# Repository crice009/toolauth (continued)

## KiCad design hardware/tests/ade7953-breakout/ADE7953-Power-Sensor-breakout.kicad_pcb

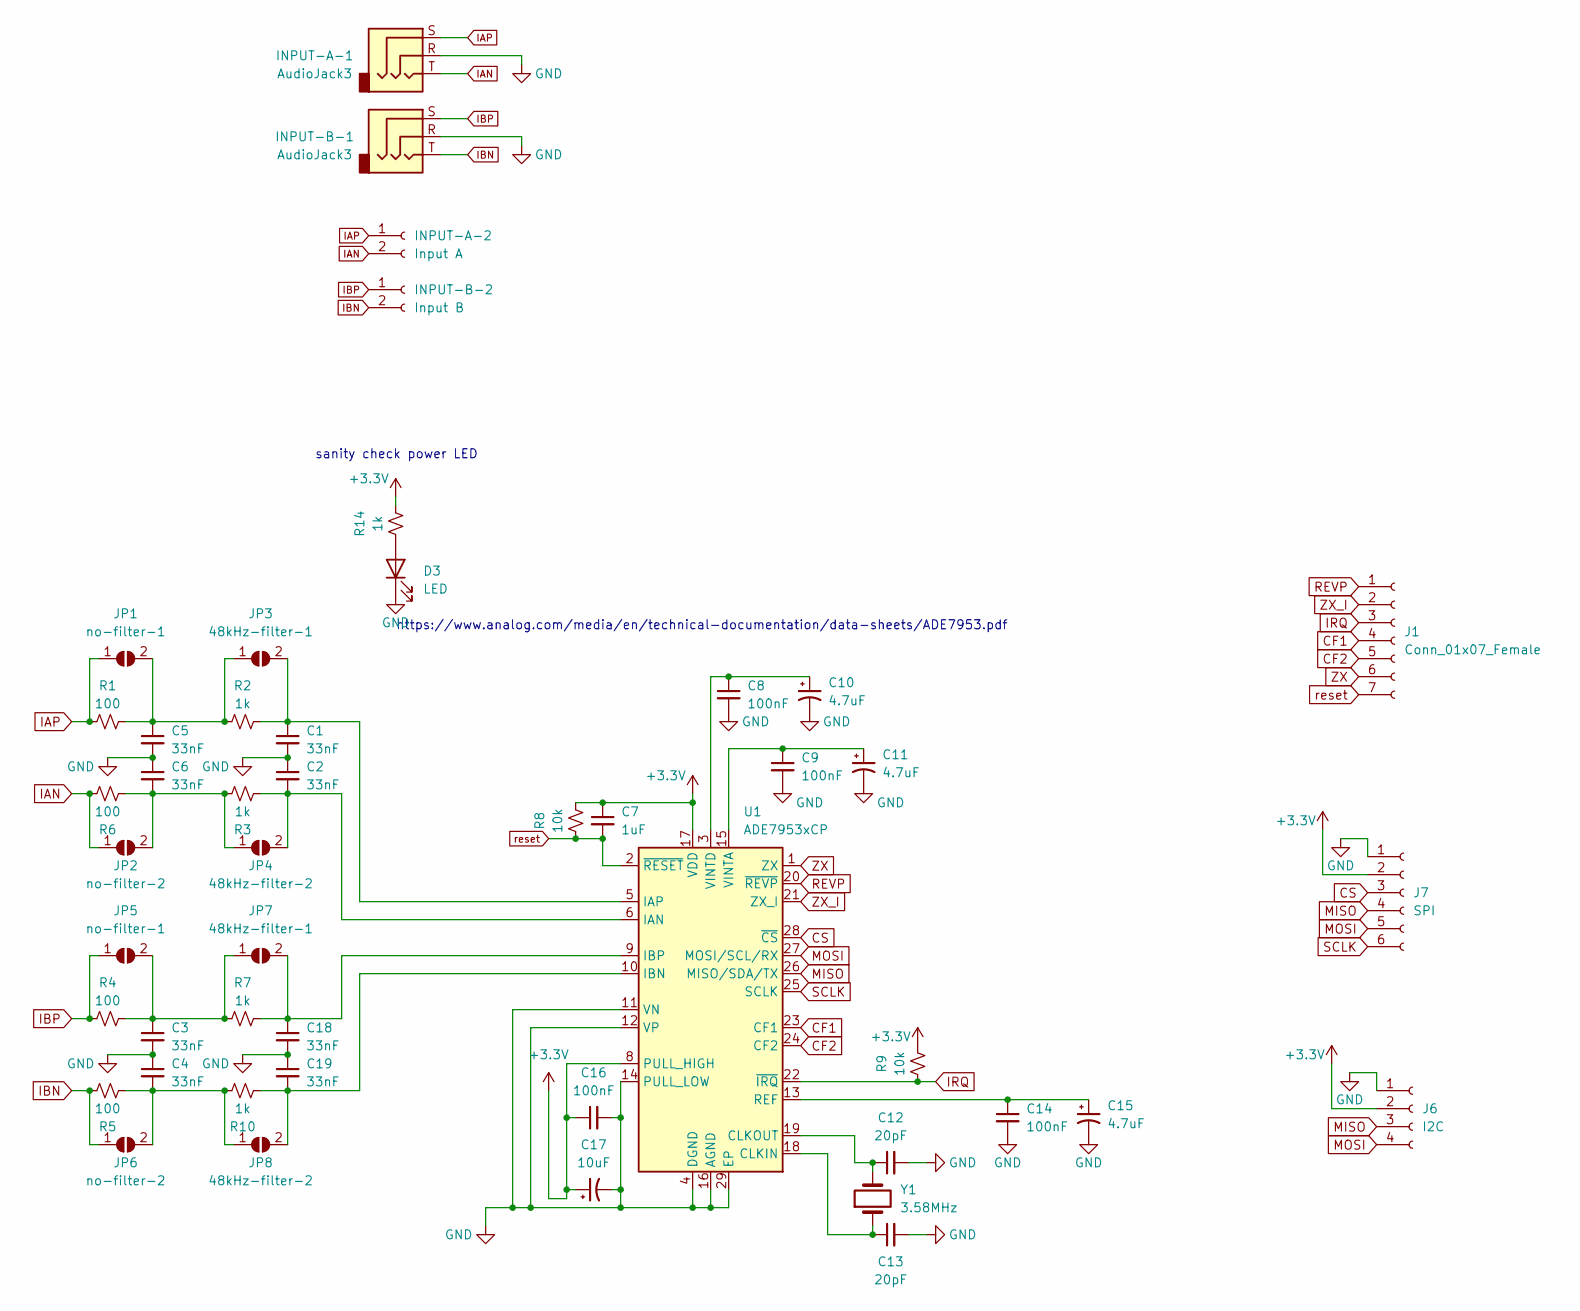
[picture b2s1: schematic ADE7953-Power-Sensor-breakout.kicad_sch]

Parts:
C1, C2, C3, C4, C5, C6, C18, C19: 33nF; C_0201_0603Metric
C7: 1uF; C_0201_0603Metric
C8, C9, C14, C16: 100nF; C_0201_0603Metric
C10, C11, C15: 4.7uF; CP_Radial_D5.0mm_P2.00mm
C12, C13: 20pF; C_0201_0603Metric
C17: 10uF; CP_Radial_D5.0mm_P2.00mm
D3: LED; LED_0201_0603Metric_Pad0.64x0.40mm_HandSolder
INPUT-A-1: AudioJack3; Jack_3.5mm_CUI_SJ1-3523N_Horizontal
INPUT-A-2: Input A; PinHeader_1x02_P2.54mm_Vertical
INPUT-B-1: AudioJack3; Jack_3.5mm_CUI_SJ1-3523N_Horizontal
INPUT-B-2: Input B; PinHeader_1x02_P2.54mm_Vertical
J1: Conn_01x07_Female; PinHeader_1x07_P2.54mm_Vertical
J6: I2C; PinHeader_1x04_P2.54mm_Vertical
J7: SPI; PinHeader_1x06_P2.54mm_Vertical
JP1, JP5: no-filter-1; SolderJumper-2_P1.3mm_Open_RoundedPad1.0x1.5mm
JP2, JP6: no-filter-2; SolderJumper-2_P1.3mm_Open_RoundedPad1.0x1.5mm
JP3, JP7: 48kHz-filter-1; SolderJumper-2_P1.3mm_Open_RoundedPad1.0x1.5mm
JP4, JP8: 48kHz-filter-2; SolderJumper-2_P1.3mm_Open_RoundedPad1.0x1.5mm
R1, R4, R5, R6: 100; R_0201_0603Metric
R2, R3, R7, R10, R14: 1k; R_0201_0603Metric
R8, R9: 10k; R_0201_0603Metric
U1: ADE7953xCP; LFCSP-28-1EP_5x5mm_P0.5mm_EP3.14x3.14mm
Y1: 3.58MHz; Crystal_HC49-4H_Vertical

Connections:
+3V3: C7.1, C16.1, C17.1, J6.2, J7.2, R8.2, R9.2, R14.2, U1.7 (PULL_HIGH), U1.8 (PULL_HIGH), U1.17 (VDD)
CF1: J1.4, U1.23 (CF1)
CF2: J1.5, U1.24 (CF2)
CS: J7.3, U1.28 (~CS)
GND: C1.2, C2.1, C3.2, C4.1, C5.2, C6.1, C8.2, C9.2, C10.2, C11.2, C12.2, C13.2, C14.2, C15.2, C16.2, C17.2, C18.2, C19.1, D3.1 (K), INPUT-A-1.R, INPUT-B-1.R, J6.1, J7.1, U1.4 (DGND), U1.11 (VN), U1.12 (VP), U1.14 (PULL_LOW), U1.16 (AGND), U1.29 (EP)
IAN: INPUT-A-1.T, INPUT-A-2.2, JP2.1 (A), R6.2
IAP: INPUT-A-1.S, INPUT-A-2.1, JP1.1 (A), R1.1
IBN: INPUT-B-1.T, INPUT-B-2.2, JP6.1 (A), R5.2
IBP: INPUT-B-1.S, INPUT-B-2.1, JP5.1 (A), R4.1
IRQ: J1.3, R9.1, U1.22 (~IRQ)
MISO: J6.3, J7.4, U1.26 (MISO/SDA/TX)
MOSI: J6.4, J7.5, U1.27 (MOSI/SCL/RX)
unnamed: C3.1, JP5.2 (B), JP7.1 (A), R4.2, R7.1
unnamed: C4.2, JP6.2 (B), JP8.1 (A), R5.1, R10.2
unnamed: C8.1, C10.1, U1.3 (VINTD)
unnamed: C9.1, C11.1, U1.15 (VINTA)
unnamed: C12.1, U1.19 (CLKOUT), Y1.2
unnamed: C13.1, U1.18 (CLKIN), Y1.1
unnamed: C14.1, C15.1, U1.13 (REF)
unnamed: D3.2 (A), R14.1
unnamed: C5.1, JP1.2 (B), JP3.1 (A), R1.2, R2.1
unnamed: C6.2, JP2.2 (B), JP4.1 (A), R3.2, R6.1
unnamed: C1.1, JP3.2 (B), R2.2, U1.5 (IAP)
unnamed: C2.2, JP4.2 (B), R3.1, U1.6 (IAN)
unnamed: C18.1, JP7.2 (B), R7.2, U1.9 (IBP)
unnamed: C19.2, JP8.2 (B), R10.1, U1.10 (IBN)
REVP: J1.1, U1.20 (~REVP)
SCLK: J7.6, U1.25 (SCLK)
ZX: J1.6, U1.1 (ZX)
ZX_I: J1.2, U1.21 (ZX_I)
reset: C7.2, J1.7, R8.1, U1.2 (~RESET)

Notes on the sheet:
sanity check power LED
https://www.analog.com/media/en/technical-documentation/data-sheets/ADE7953.pdf

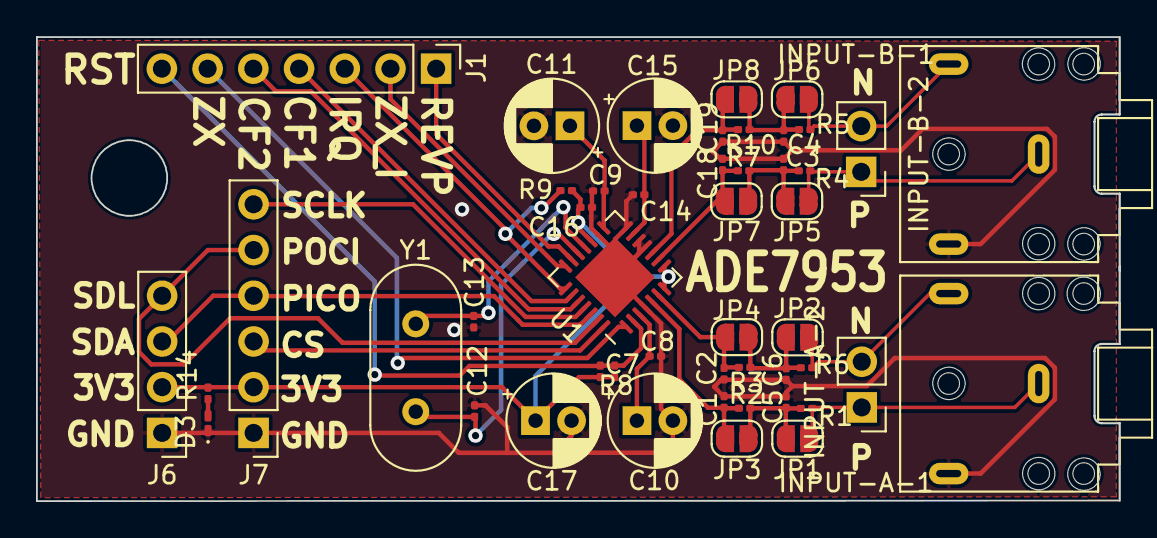
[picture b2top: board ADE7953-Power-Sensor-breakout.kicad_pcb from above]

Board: 2 copper layers, 60.1 x 25.8 mm, 48 parts (0 on the bottom side), 31 nets.

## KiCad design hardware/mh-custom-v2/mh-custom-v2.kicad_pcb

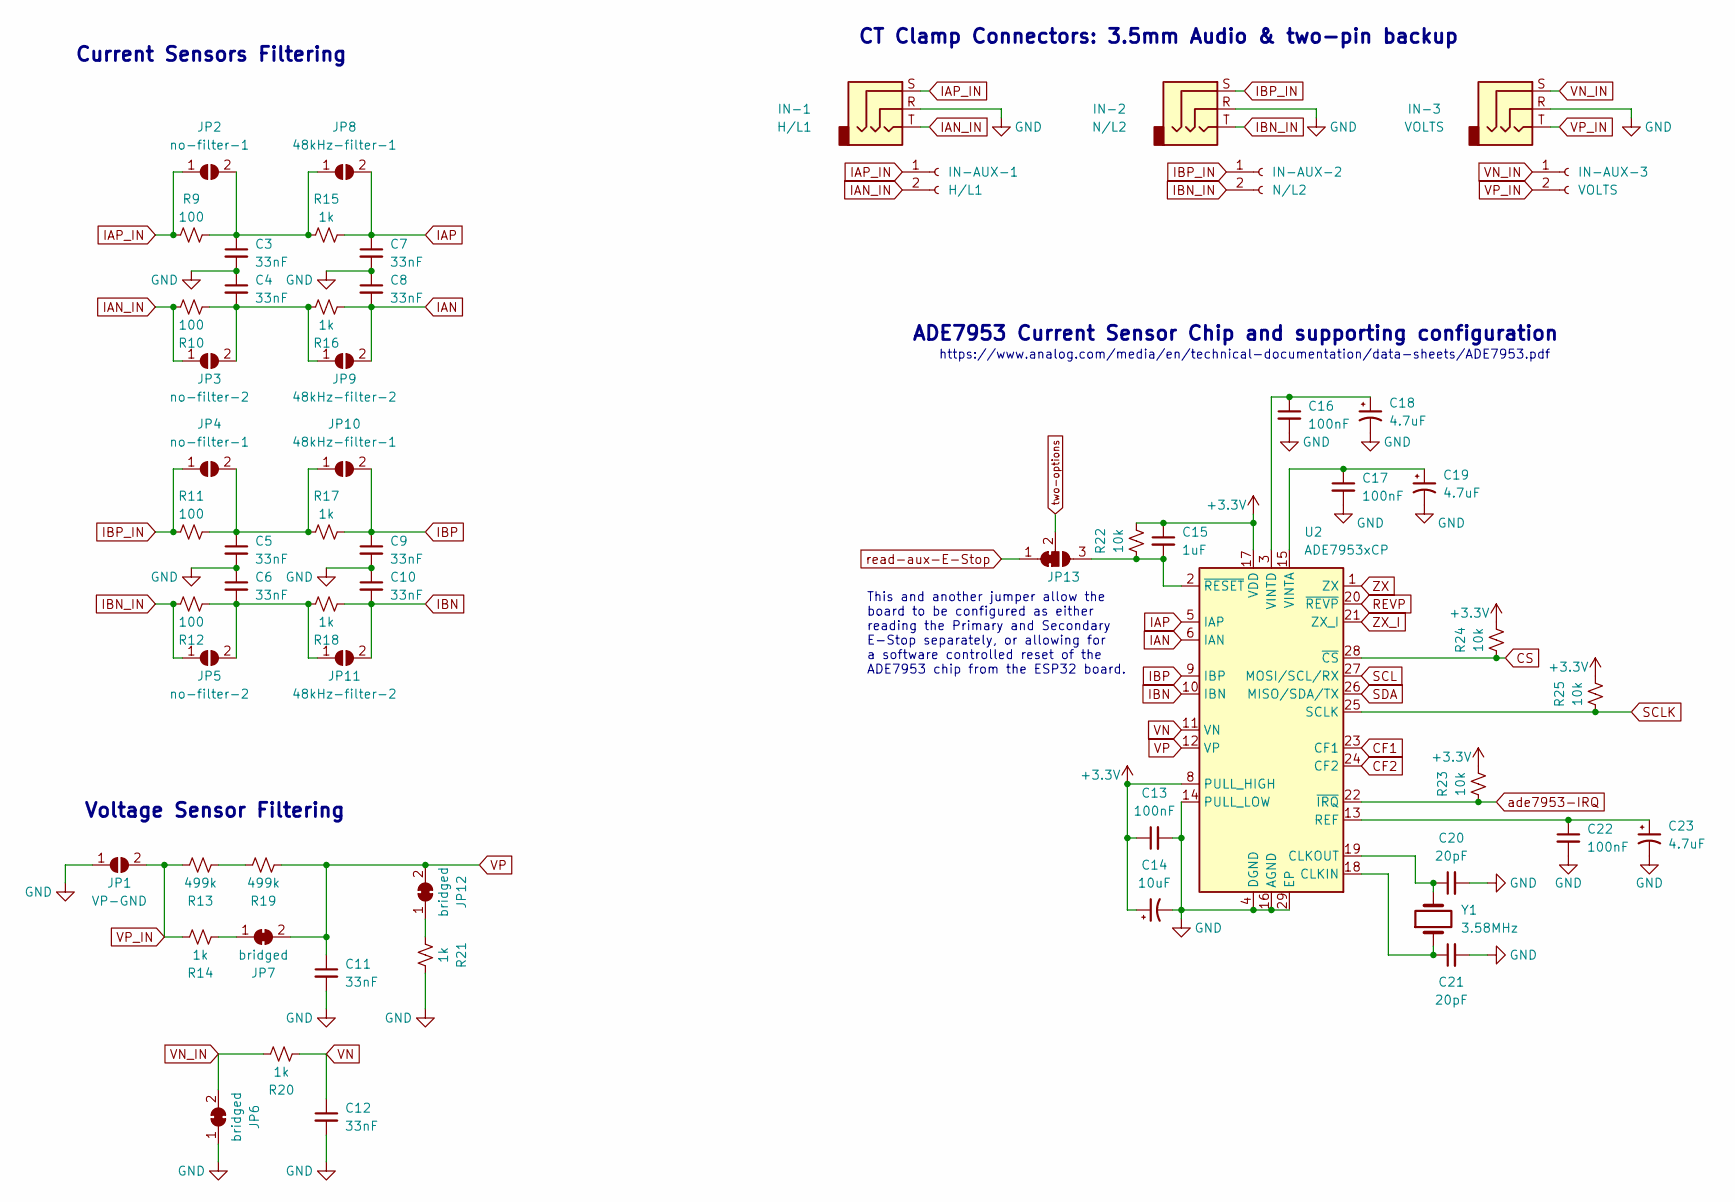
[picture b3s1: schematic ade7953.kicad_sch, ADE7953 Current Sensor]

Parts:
C3, C4, C5, C6, C7, C8, C9, C10, C11, C12: 33nF; LED_0603_1608Metric; JLCPCB Part # C21117
C13, C16, C17, C22: 100nF; LED_0603_1608Metric; JLCPCB Part # C14663
C14: 10uF; CP_Radial_D5.0mm_P2.00mm; JLCPCB Part # C88726
C15: 1uF; LED_0603_1608Metric; JLCPCB Part # C15849
C18, C19, C23: 4.7uF; CP_Radial_D5.0mm_P2.00mm; JLCPCB Part # C88759
C20, C21: 20pF; LED_0603_1608Metric; JLCPCB Part # C1648
IN-1: H/L1; Jack_3.5mm_CUI_SJ1-3525N_Horizontal; JLCPCB Part # C692542
IN-2: N/L2; Jack_3.5mm_CUI_SJ1-3525N_Horizontal; JLCPCB Part # C692542
IN-3: VOLTS; Jack_3.5mm_CUI_SJ1-3525N_Horizontal; JLCPCB Part # C692542
IN-AUX-1: H/L1; PinHeader_1x02_P2.54mm_Vertical
IN-AUX-2: N/L2; PinHeader_1x02_P2.54mm_Vertical
IN-AUX-3: VOLTS; PinHeader_1x02_P2.54mm_Vertical
JP1: VP-GND; SolderJumper-2_P1.3mm_Open_RoundedPad1.0x1.5mm
JP2, JP4: no-filter-1; SolderJumper-2_P1.3mm_Open_RoundedPad1.0x1.5mm
JP3, JP5: no-filter-2; SolderJumper-2_P1.3mm_Open_RoundedPad1.0x1.5mm
JP6, JP7, JP12: bridged; SolderJumper-2_P1.3mm_Bridged_RoundedPad1.0x1.5mm
JP8, JP10: 48kHz-filter-1; SolderJumper-2_P1.3mm_Open_RoundedPad1.0x1.5mm
JP9, JP11: 48kHz-filter-2; SolderJumper-2_P1.3mm_Open_RoundedPad1.0x1.5mm
JP13: SolderJumper_3_Bridged12; SolderJumper-3_P1.3mm_Bridged12_RoundedPad1.0x1.5mm
R9, R10, R11, R12: 100; R_0603_1608Metric; JLCPCB Part # C22775
R13, R19: 499k; R_0603_1608Metric; JLCPCB Part # C131054
R14, R15, R16, R17, R18, R20, R21: 1k; R_0603_1608Metric; JLCPCB Part # C21190
R22, R23, R24, R25: 10k; R_0603_1608Metric; JLCPCB Part # C25804
U2: ADE7953xCP; LFCSP-28-1EP_5x5mm_P0.5mm_EP3.14x3.14mm; JLCPCB Part # C515890
Y1: 3.58MHz; Crystal_HC49-4H_Vertical; JLCPCB Part # C2826865

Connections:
+3.3V: C13.1, C14.1, C15.1, R22.2, R23.2, R24.2, R25.2, U2.7 (PULL_HIGH), U2.8 (PULL_HIGH), U2.17 (VDD); also elsewhere on the board
CF1: U2.23 (CF1)
CF2: U2.24 (CF2)
CS: R24.1, U2.28 (~CS)
GND: C3.2, C4.1, C5.2, C6.1, C7.2, C8.1, C9.2, C10.1, C11.2, C12.2, C13.2, C14.2, C16.2, C17.2, C18.2, C19.2, C20.2, C21.2, C22.2, C23.2, IN-1.R, IN-2.R, IN-3.R, JP1.1 (A), JP6.1 (A), R21.2, U2.4 (DGND), U2.14 (PULL_LOW), U2.16 (AGND), U2.29 (EP); also elsewhere on the board
IAN: C8.2, JP9.2 (B), R16.1, U2.6 (IAN)
IAN_IN: IN-1.T, IN-AUX-1.2, JP3.1 (A), R10.2
IAP: C7.1, JP8.2 (B), R15.2, U2.5 (IAP)
IAP_IN: IN-1.S, IN-AUX-1.1, JP2.1 (A), R9.1
IBN: C10.2, JP11.2 (B), R18.1, U2.10 (IBN)
IBN_IN: IN-2.T, IN-AUX-2.2, JP5.1 (A), R12.2
IBP: C9.1, JP10.2 (B), R17.2, U2.9 (IBP)
IBP_IN: IN-2.S, IN-AUX-2.1, JP4.1 (A), R11.1
unnamed: C3.1, JP2.2 (B), JP8.1 (A), R9.2, R15.1
unnamed: C4.2, JP3.2 (B), JP9.1 (A), R10.1, R16.2
unnamed: C5.1, JP4.2 (B), JP10.1 (A), R11.2, R17.1
unnamed: C6.2, JP5.2 (B), JP11.1 (A), R12.1, R18.2
unnamed: C15.2, JP13.3 (B), R22.1, U2.2 (~RESET)
unnamed: C16.1, C18.1, U2.3 (VINTD)
unnamed: C17.1, C19.1, U2.15 (VINTA)
unnamed: C20.1, U2.19 (CLKOUT), Y1.2
unnamed: C21.1, U2.18 (CLKIN), Y1.1
unnamed: C22.1, C23.1, U2.13 (REF)
unnamed: JP7.1 (A), R14.1
unnamed: JP12.1 (A), R21.1
unnamed: R13.1, R19.2
REVP: U2.20 (~REVP)
SCL: U2.27 (MOSI/SCL/RX); also elsewhere on the board
SCLK: R25.1, U2.25 (SCLK)
SDA: U2.26 (MISO/SDA/TX); also elsewhere on the board
VN: C12.1, R20.1, U2.11 (VN)
VN_IN: IN-3.S, IN-AUX-3.1, JP6.2 (B), R20.2
VP: C11.1, JP7.2 (B), JP12.2 (B), R19.1, U2.12 (VP)
VP_IN: IN-3.T, IN-AUX-3.2, JP1.2 (B), R13.2, R14.2
ZX: U2.1 (ZX)
ZX_I: U2.21 (ZX_I)
ade7953-IRQ: R23.1, U2.22 (~IRQ); also elsewhere on the board
read-aux-E-Stop: JP13.1 (A); also elsewhere on the board
two-options: JP13.2 (C); also elsewhere on the board

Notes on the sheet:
CT Clamp Connectors: 3.5mm Audio & two-pin backup
Voltage Sensor Filtering
https://www.analog.com/media/en/technical-documentation/data-sheets/ADE7953.pdf
ADE7953 Current Sensor Chip and supporting configuration
Current Sensors Filtering
This and another jumper allow the board to be configured as either reading the Primary and Secondary E-Stop separately, or allowing for a software controlled reset of the ADE7953 chip from the ESP32 board.

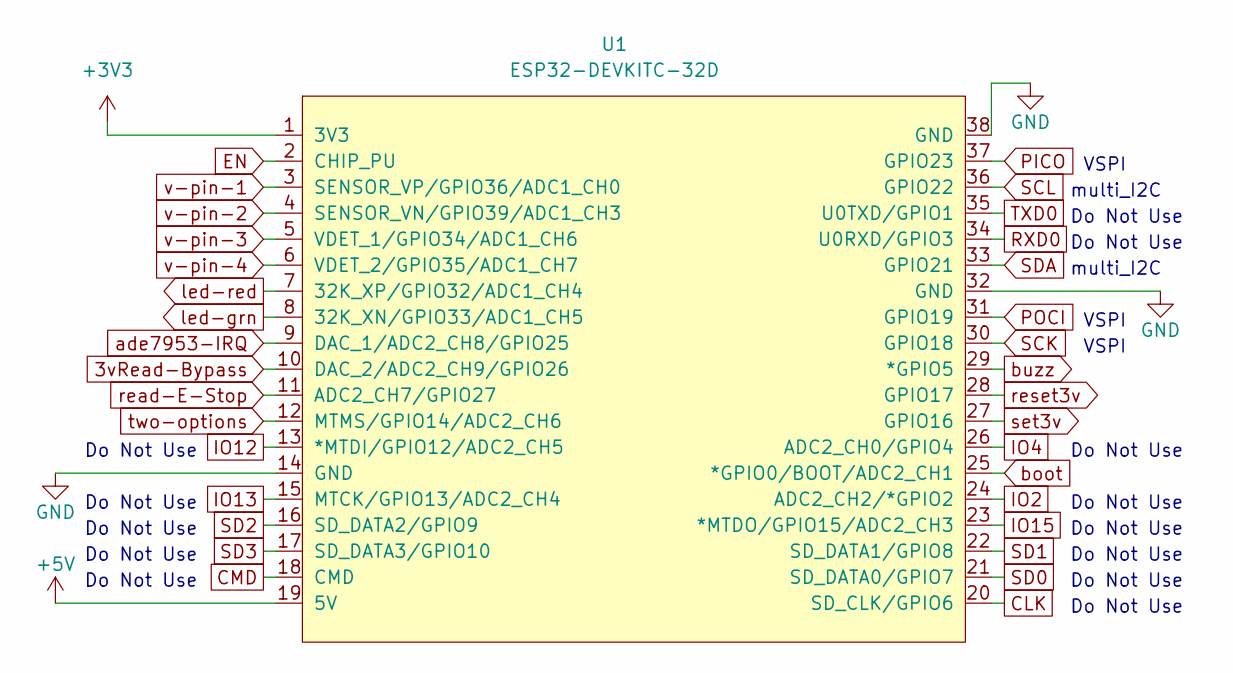
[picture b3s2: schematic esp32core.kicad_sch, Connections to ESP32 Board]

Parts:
U1: ESP32-DEVKITC-32D; ESP32-DevKitC; PARTREV 4

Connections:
unnamed: U1.14 (GND), U1.32 (GND), U1.38 (GND)

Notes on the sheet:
Do Not Use
VSPI
multi_I2C

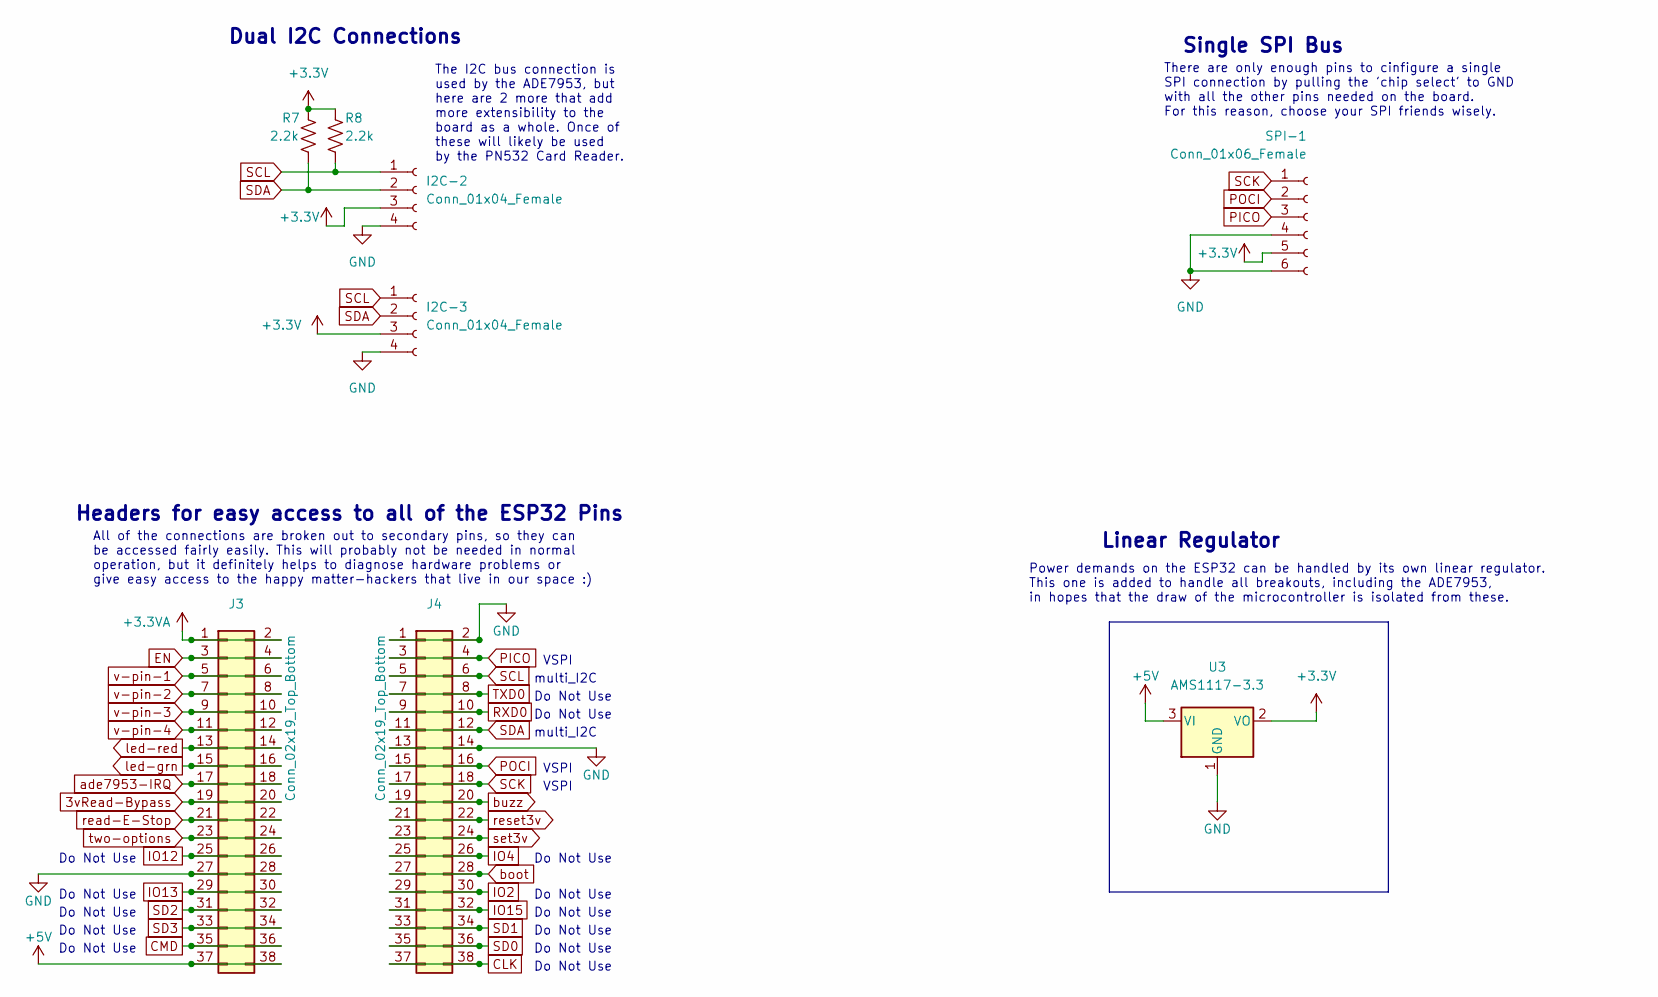
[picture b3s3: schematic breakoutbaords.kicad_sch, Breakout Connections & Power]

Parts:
I2C-2, I2C-3: Conn_01x04_Female; JST_PH_B4B-PH-K_1x04_P2.00mm_Vertical; JLCPCB Part # C131334
J3, J4: Conn_02x19_Top_Bottom; PinSocket_2x19_P2.54mm_Vertical; JLCPCB Part # C2897420
R7, R8: 2.2k; R_0603_1608Metric; JLCPCB Part # C4190
SPI-1: Conn_01x06_Female; JST_PH_B6B-PH-K_1x06_P2.00mm_Vertical; JLCPCB Part # C131342
U3: AMS1117-3.3; SOT-223-3_TabPin2; JLCPCB Part # C6186

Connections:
3vRead-Bypass: J3.19, J3.20; also elsewhere on the board
+3.3V: I2C-2.3, I2C-3.3, R7.2, R8.2, SPI-1.5, U3.2 (VO); also elsewhere on the board
+3.3VA: J3.1, J3.2; also elsewhere on the board
+5V: J3.37, J3.38, U3.3 (VI); also elsewhere on the board
CLK: J4.37, J4.38
CMD: J3.35, J3.36
EN: J3.3, J3.4; also elsewhere on the board
GND: I2C-2.4, I2C-3.4, J3.27, J3.28, J4.1, J4.2, J4.13, J4.14, SPI-1.4, SPI-1.6, U3.1 (GND); also elsewhere on the board
IO2: J4.29, J4.30
IO4: J4.25, J4.26
IO12: J3.25, J3.26
IO13: J3.29, J3.30
IO15: J4.31, J4.32
PICO: J4.3, J4.4, SPI-1.3
POCI: J4.15, J4.16, SPI-1.2
RXD0: J4.9, J4.10
SCK: J4.17, J4.18, SPI-1.1
SCL: I2C-2.1, I2C-3.1, J4.5, J4.6, R8.1; also elsewhere on the board
SD0: J4.35, J4.36
SD1: J4.33, J4.34
SD2: J3.31, J3.32
SD3: J3.33, J3.34
SDA: I2C-2.2, I2C-3.2, J4.11, J4.12, R7.1; also elsewhere on the board
TXD0: J4.7, J4.8
ade7953-IRQ: J3.17, J3.18; also elsewhere on the board
boot: J4.27, J4.28; also elsewhere on the board
buzz: J4.19, J4.20; also elsewhere on the board
led-grn: J3.15, J3.16; also elsewhere on the board
led-red: J3.13, J3.14; also elsewhere on the board
read-E-Stop: J3.21, J3.22; also elsewhere on the board
reset3v: J4.21, J4.22; also elsewhere on the board
set3v: J4.23, J4.24; also elsewhere on the board
two-options: J3.23, J3.24; also elsewhere on the board
v-pin-1: J3.5, J3.6; also elsewhere on the board
v-pin-2: J3.7, J3.8; also elsewhere on the board
v-pin-3: J3.9, J3.10; also elsewhere on the board
v-pin-4: J3.11, J3.12; also elsewhere on the board

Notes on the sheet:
VSPI
Single SPI Bus
Do Not Use
All of the connections are broken out to secondary pins, so they can be accessed fairly easily. This will probably not be needed in normal operation, but it definitely helps to diagnose hardware problems or give easy access to the happy matter-hackers that live in our space :)
Power demands on the ESP32 can be handled by its own linear regulator. This one is added to handle all breakouts, including the ADE7953, in hopes that the draw of the microcontroller is isolated from these.
multi_I2C
Dual I2C Connections
Linear Regulator
The I2C bus connection is used by the ADE7953, but here are 2 more that add more extensibility to the board as a whole. Once of these will likely be used by the PN532 Card Reader.
There are only enough pins to cinfigure a single SPI connection by pulling the 'chip select' to GND with all the other pins needed on the board. For this reason, choose your SPI friends wisely.
Headers for easy access to all of the ESP32 Pins

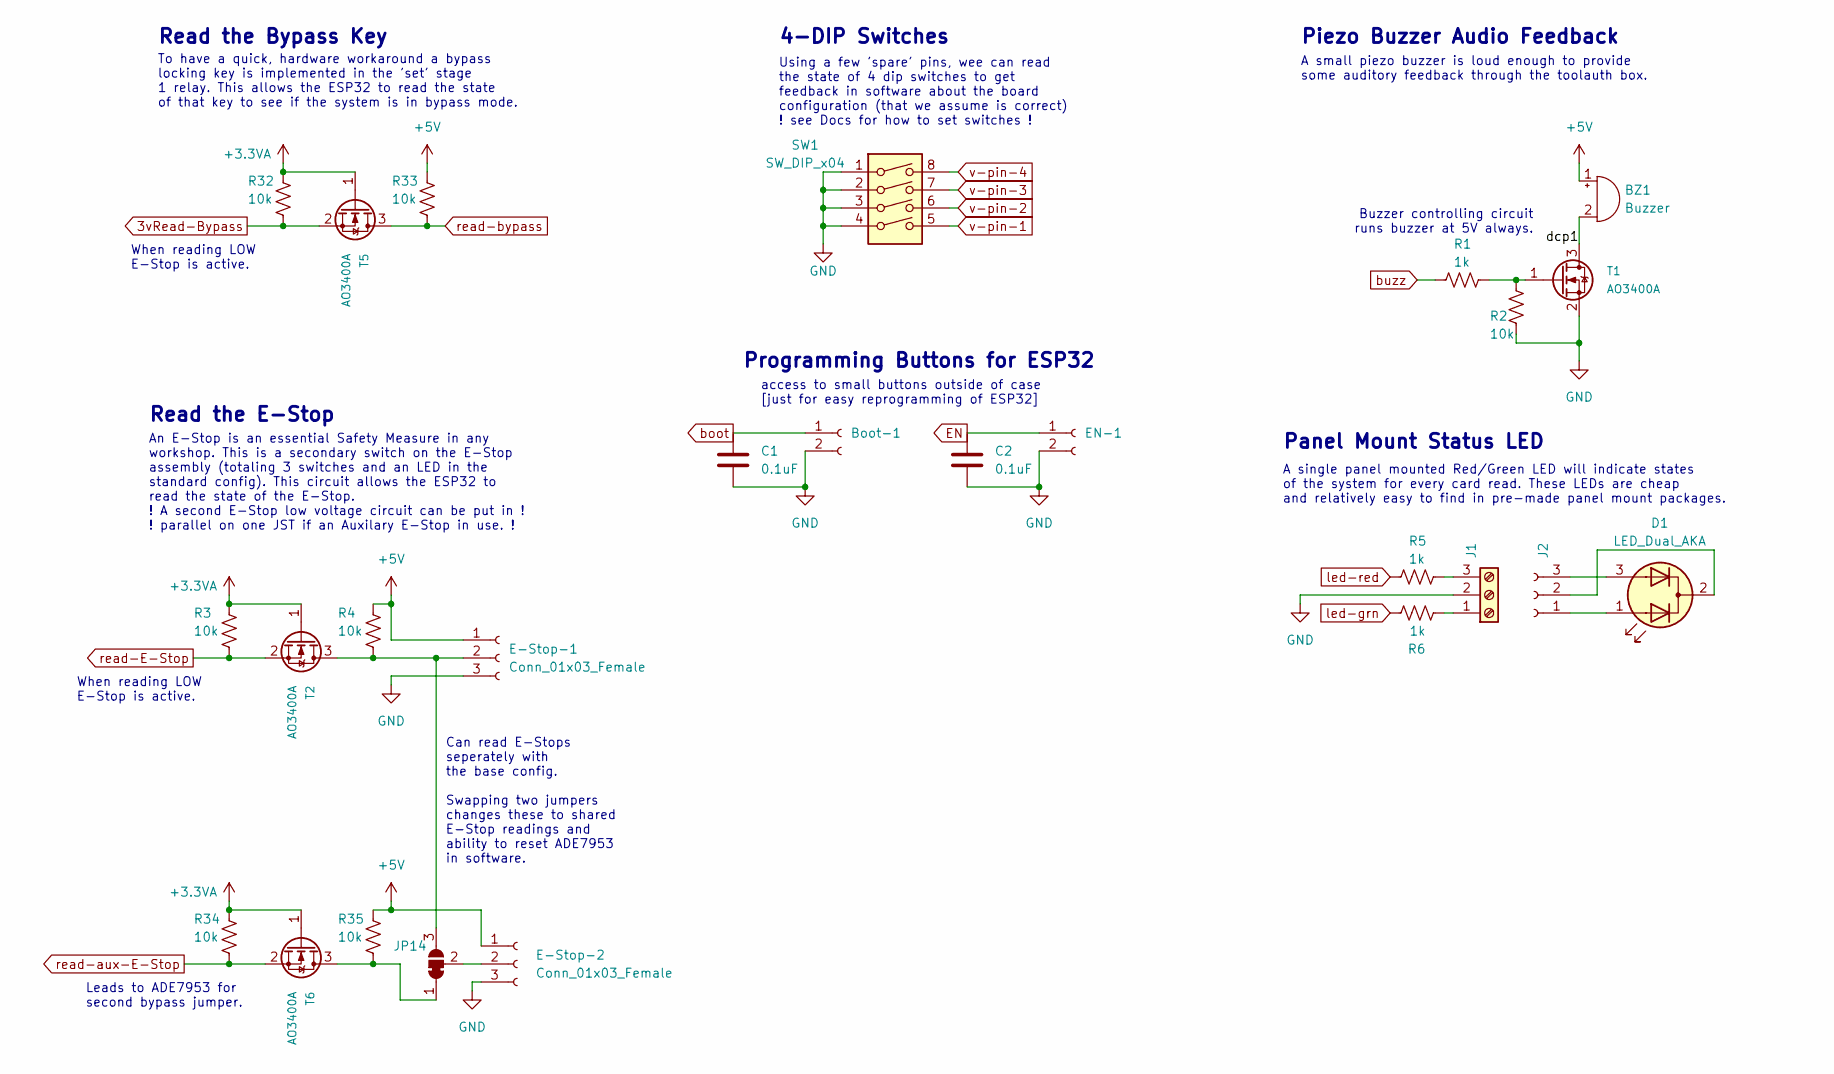
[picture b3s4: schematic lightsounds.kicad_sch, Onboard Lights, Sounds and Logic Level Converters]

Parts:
BZ1: Buzzer; Buzzer_12x9.5RM7.6; JLCPCB Part # C96095
Boot-1: Conn_01x02_Female; PinSocket_1x02_P2.54mm_Vertical
C1, C2: 0.1uF; LED_0603_1608Metric; JLCPCB Part # C14663
D1: LED_Dual_AKA
E-Stop-1, E-Stop-2: Conn_01x03_Female; JST_PH_B3B-PH-K_1x03_P2.00mm_Vertical; JLCPCB Part # C131339
EN-1: Conn_01x02_Female; PinSocket_1x02_P2.54mm_Vertical
J1: Conn_01x03_Male; TerminalBlock_TE_282834-3_1x03_P2.54mm_Horizontal; JLCPCB Part # C557686
J2: Conn_01x03_Female
JP14: SolderJumper_3_Bridged12; SolderJumper-3_P1.3mm_Bridged12_RoundedPad1.0x1.5mm
R1, R5, R6: 1k; R_0603_1608Metric; JLCPCB Part # C21190
R2, R3, R4, R32, R33, R34, R35: 10k; R_0603_1608Metric; JLCPCB Part # C25804
SW1: SW_DIP_x04; SW_DIP_SPSTx04_Slide_Omron_A6H-4101_W6.15mm_P1.27mm; JLCPCB Part # C224996
T1, T2, T5, T6: AO3400A; SOT-23; JLCPCB Part # C427382

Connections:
3vRead-Bypass: R32.1, T5.2 (S); also elsewhere on the board
+3.3VA: R3.2, R32.2, R34.2, T2.1 (G), T5.1 (G), T6.1 (G); also elsewhere on the board
+5V: BZ1.1 (-), E-Stop-1.1, E-Stop-2.1, R4.2, R33.2, R35.2; also elsewhere on the board
/microcontroller/lightsounds/dcp1: BZ1.2 (+), T1.3 (D)
EN: C2.1, EN-1.1; also elsewhere on the board
GND: Boot-1.2, C1.2, C2.2, E-Stop-1.3, E-Stop-2.3, EN-1.2, J1.2, R2.1, SW1.1, SW1.2, SW1.3, SW1.4, T1.2 (S); also elsewhere on the board
unnamed: D1.1 (A1), J2.1
unnamed: D1.2 (K), J2.2
unnamed: D1.3 (A2), J2.3
unnamed: E-Stop-1.2, JP14.3 (B), R4.1, T2.3 (D)
unnamed: E-Stop-2.2, JP14.2 (C)
unnamed: J1.1, R6.1
unnamed: J1.3, R5.2
unnamed: JP14.1 (A), R35.1, T6.3 (D)
unnamed: R1.2, R2.2, T1.1 (G)
boot: Boot-1.1, C1.1; also elsewhere on the board
buzz: R1.1; also elsewhere on the board
led-grn: R6.2; also elsewhere on the board
led-red: R5.1; also elsewhere on the board
read-E-Stop: R3.1, T2.2 (S); also elsewhere on the board
read-aux-E-Stop: R34.1, T6.2 (S); also elsewhere on the board
read-bypass: R33.1, T5.3 (D); also elsewhere on the board
v-pin-1: SW1.5; also elsewhere on the board
v-pin-2: SW1.6; also elsewhere on the board
v-pin-3: SW1.7; also elsewhere on the board
v-pin-4: SW1.8; also elsewhere on the board

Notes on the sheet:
Programming Buttons for ESP32
Leads to ADE7953 for second bypass jumper.
4-DIP Switches
A single panel mounted Red/Green LED will indicate states of the system for every card read. These LEDs are cheap and relatively easy to find in pre-made panel mount packages.
Can read E-Stops seperately with the base config. Swapping two jumpers changes these to shared E-Stop readings and ability to reset ADE7953 in software.
A small piezo buzzer is loud enough to provide some auditory feedback through the toolauth box.
access to small buttons outside of case [just for easy reprogramming of ESP32]
Read the E-Stop
When reading LOW E-Stop is active.
An E-Stop is an essential Safety Measure in any workshop. This is a secondary switch on the E-Stop assembly (totaling 3 switches and an LED in the standard config). This circuit allows the ESP32 to read the state of the E-Stop. ! A second E-Stop low voltage circuit can be put in ! ! parallel on one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
Buzzer controlling circuit runs buzzer at 5V always.
To have a quick, hardware workaround a bypass locking key is implemented in the 'set' stage 1 relay. This allows the ESP32 to read the state of that key to see if the system is in bypass mode.
Piezo Buzzer Audio Feedback
Panel Mount Status LED
Using a few 'spare' pins, wee can read the state of 4 dip switches to get feedback in software about the board configuration (that we assume is correct) ! see Docs for how to set switches !
Read the Bypass Key

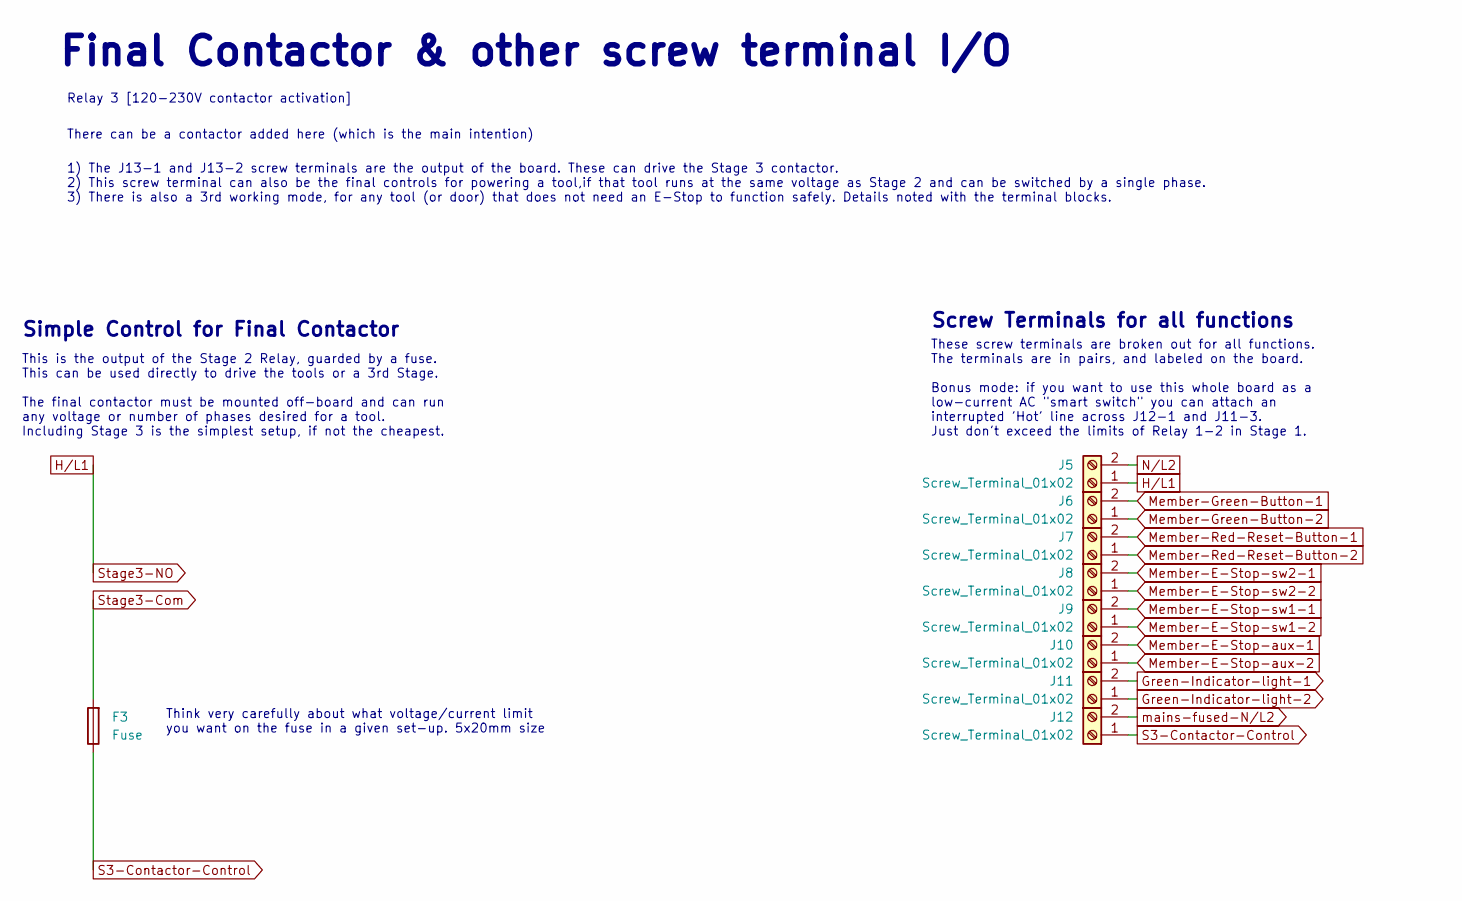
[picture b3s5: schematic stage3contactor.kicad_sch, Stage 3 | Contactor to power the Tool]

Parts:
F3: Fuse; Fuseholder_Cylinder-5x20mm_Stelvio-Kontek_PTF78_Horizontal_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; JLCPCB Part # C717030
J5, J6, J7, J8, J9, J10, J11, J12: Screw_Terminal_01x02; TerminalBlock_Altech_AK300-2_P5.00mm; JLCPCB Part # C8269

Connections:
Green-Indicator-light-1: J11.2; also elsewhere on the board
Green-Indicator-light-2: F3.2, J11.1; also elsewhere on the board
H/L1: J5.1; also elsewhere on the board
Member-E-Stop-aux-2: J10.1; also elsewhere on the board
Member-E-Stop-sw2-2: J8.1; also elsewhere on the board
Member-Red-Reset-Button-1: J7.2; also elsewhere on the board
N/L2: J5.2; also elsewhere on the board
S3-Contactor-Control: F3.1, J12.1
mains-fused-N/L2: J12.2; also elsewhere on the board

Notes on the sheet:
Final Contactor & other screw terminal I/O
These screw terminals are broken out for all functions. The terminals are in pairs, and labeled on the board. Bonus mode: if you want to use this whole board as a low-current AC "smart switch" you can attach an interrupted 'Hot' line across J12-1 and J11-3. Just don't exceed the limits of Relay 1-2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
This is the output of the Stage 2 Relay, guarded by a fuse. This can be used directly to drive the tools or a 3rd Stage. The final contactor must be mounted off-board and can run any voltage or number of phases desired for a tool. Including Stage 3 is the simplest setup, if not the cheapest.
Think very carefully about what voltage/current limit you want on the fuse in a given set-up. 5x20mm size
Relay 3 [120-230V contactor activation]
There can be a contactor added here (which is the main intention)
1) The J13-1 and J13-2 screw terminals are the output of the board. These can drive the Stage 3 contactor. 2) This screw terminal can also be the final controls for powering a tool,if that tool runs at the same voltage as Stage 2 and can be switched by a single phase. 3) There is also a 3rd working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
Simple Control for Final Contactor
Screw Terminals for all functions

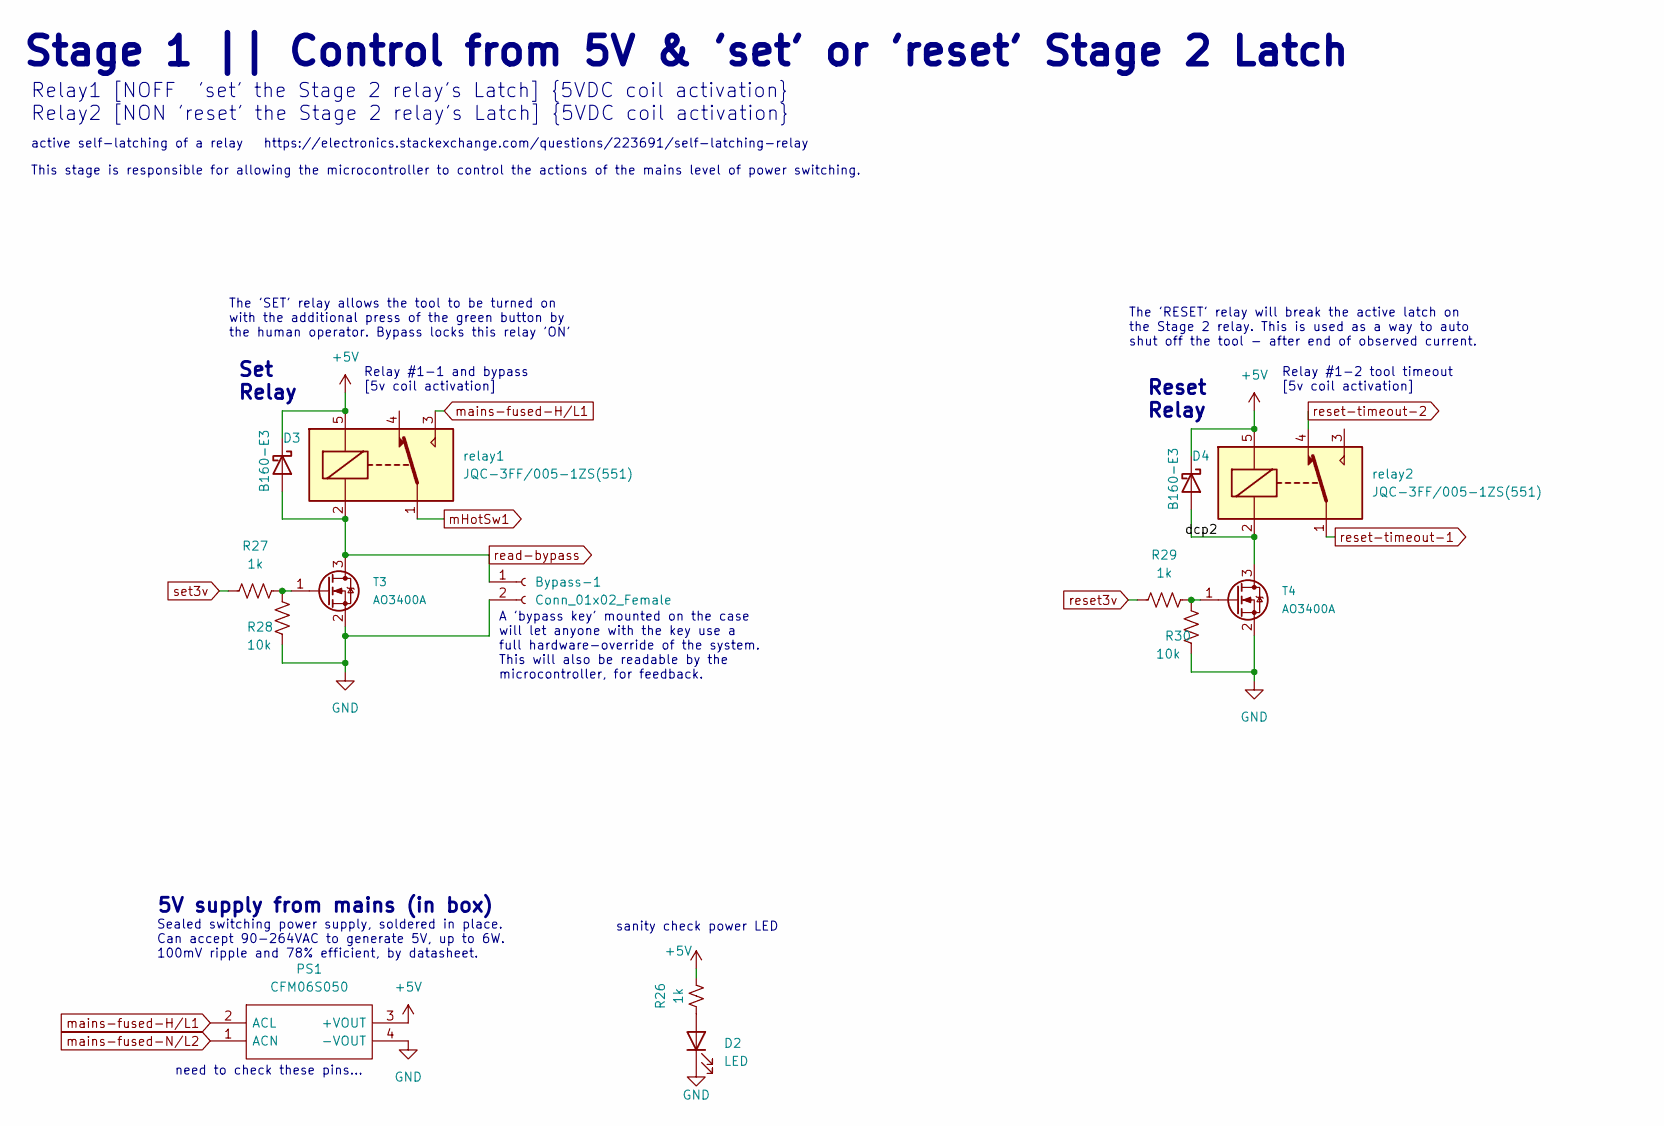
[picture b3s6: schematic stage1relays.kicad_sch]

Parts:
Bypass-1: Conn_01x02_Female; JST_PH_B2B-PH-K_1x02_P2.00mm_Vertical; JLCPCB Part # C131337
D2: LED; LED_0603_1608Metric; JLCPCB Part # C2286
D3, D4: B160-E3; D_SMA; JLCPCB Part # C24784
PS1: CFM06S050; CFM06S050E; Mouser Part Number 418-CFM06S050-E
R26, R27, R29: 1k; R_0603_1608Metric; JLCPCB Part # C21190
R28, R30: 10k; R_0603_1608Metric; JLCPCB Part # C25804
T3, T4: AO3400A; SOT-23; JLCPCB Part # C427382
relay1, relay2: JQC-3FF/005-1ZS(551); Relay_SPDT_SANYOU_SRD_Series_Form_C; JLCPCB Part # C9221

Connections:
+5V: D3.1 (K), D4.1 (K), PS1.3 (+VOUT), R26.2, relay1.5, relay2.5; also elsewhere on the board
/mainslevelcontrol/stage1relays/dcp2: D4.2 (A), T4.3 (D), relay2.2
GND: Bypass-1.2, D2.1 (K), PS1.4 (-VOUT), R28.2, R30.2, T3.2 (S), T4.2 (S); also elsewhere on the board
Member-Red-Reset-Button-1: PS1.2 (ACL), relay1.3; also elsewhere on the board
unnamed: D2.2 (A), R26.1
unnamed: R27.2, R28.1, T3.1 (G)
unnamed: R29.2, R30.1, T4.1 (G)
mains-fused-N/L2: PS1.1 (ACN); also elsewhere on the board
read-bypass: Bypass-1.1, D3.2 (A), T3.3 (D), relay1.2; also elsewhere on the board
reset3v: R29.1; also elsewhere on the board
set3v: R27.1; also elsewhere on the board

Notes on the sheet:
The 'SET' relay allows the tool to be turned on with the additional press of the green button by the human operator. Bypass locks this relay 'ON'
The 'RESET' relay will break the active latch on the Stage 2 relay. This is used as a way to auto shut off the tool - after end of observed current.
need to check these pins...
Relay #1-2 tool timeout [5v coil activation]
Sealed switching power supply, soldered in place. Can accept 90-264VAC to generate 5V, up to 6W. 100mV ripple and 78% efficient, by datasheet.
Stage 1 || Control from 5V & 'set' or 'reset' Stage 2 Latch
Set Relay
Reset Relay
sanity check power LED
Relay1 [NOFF 'set' the Stage 2 relay's Latch] {5VDC coil activation} Relay2 [NON 'reset' the Stage 2 relay's Latch] {5VDC coil activation}
active self-latching of a relay https://electronics.stackexchange.com/questions/223691/self-latching-relay
A 'bypass key' mounted on the case will let anyone with the key use a full hardware-override of the system. This will also be readable by the microcontroller, for feedback.
This stage is responsible for allowing the microcontroller to control the actions of the mains level of power switching.
5V supply from mains (in box)
Relay #1-1 and bypass [5v coil activation]
